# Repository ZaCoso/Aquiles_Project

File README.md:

# 🦿 AQUILES - Exoesqueleto de Asistencia Motriz

<div align="center">
  
  <h3>Revolucionando la movilidad humana</h3>
  <p>Exoesqueleto de asistencia motora con inteligencia artificial y control FOC</p>

  <p align="center">
    &nbsp;
    &nbsp;
    &nbsp;
    &nbsp;
    
  </p>
</div>

---

## 🌍 ¿Qué es AQUILES?

**AQUILES** es un exoesqueleto de asistencia motriz desarrollado por estudiantes de **Aviónica de la Escuela Técnica N.º 7 “IMPA” de Quilmes**, cuyo objetivo es **reducir la fatiga, mejorar la estabilidad y otorgar mayor autonomía** a personas con dificultades de movilidad.

El sistema combina **electrónica de control avanzada**, **inteligencia artificial adaptativa** y **una arquitectura de motores BLDC con control FOC**, optimizando la asistencia durante la marcha según el esfuerzo y ritmo del usuario.  
Incluye una **aplicación móvil y plataforma web** para el monitoreo, ajuste remoto y registro de datos clínicos en tiempo real.

---
## 🎬 Video Presentación
<p align="center">
  
  <br/>
  <em>Ver en YouTube</em>
</p>

---
## 🧠 Propósito e Impacto

AQUILES busca democratizar el acceso a tecnologías de rehabilitación avanzadas y accesibles en Argentina y Latinoamérica.  
Su impacto se extiende en tres ejes principales:

- **Médico:** mejora la eficacia de procesos de rehabilitación neuromotriz.  
- **Social:** promueve la autonomía e inclusión de personas con movilidad reducida.  
- **Tecnológico:** posiciona al país como referente en robótica de asistencia y salud.

---

## ⚙️ Arquitectura del Sistema

### 🔩 Hardware
- **Microcontrolador principal:** ESP32-S3 (Wi-Fi, BLE, USB OTG, dual-core LX7 240 MHz).  
- **Drivers de motor:** módulos basados en **IR2104 + MOSFETs IRLR7843** controlados por **RP2040**.  
- **Motores:** BLDC con reductoras planetarias de 4 etapas.  
- **Sensores:**
  - Encoders magnéticos **AS5600 / AS5048A**.  
  - Sensores de corriente **ACS725**.  
  - IMU **MPU-6050**.  
- **Fuente de alimentación:** baterías Li-Po 3S 5000 mAh 70C.  
- **Estructura:** piezas en **PETG** con insertos metálicos y módulos intercambiables (Athena, Drive-M, Módulos motrices).

### 💻 Software
- **Lenguajes:** C, C++, Dart, HTML, JS.  
- **Firmware:** SimpleFOC, comunicación SPI entre ESP32-S3 y RP2040.  
- **App móvil:** desarrollada en **Flutter + Firebase**, con UI intuitiva para monitoreo y ajustes.  
- **Web:** [zacas-code.github.io/Host_Aquiles_Project](https://zacas-code.github.io/Host_Aquiles_Project/) – presentación del ecosistema, galería, sponsors y contacto.

---

## 📱 Aplicación Móvil – *AquilesApp*

La app permite:
- Conectar el exoesqueleto vía BLE.  
- Ajustar el nivel de asistencia y sensibilidad.  
- Visualizar batería, torque y consumo en tiempo real.  
- Registrar sesiones de rehabilitación.  
- Generar informes automáticos para médicos y terapeutas.

Desarrollada en **Flutter**, con base de datos en **Firebase Firestore**, integración de **autenticación segura** y **almacenamiento en la nube**.

---

## 🦾 Módulos Principales

| Módulo | Descripción |
|--------|-------------|
| **Athena** | Núcleo de control. Alberga la mainboard, conectividad y algoritmo central. |
| **Drive-M** | Controladores locales con RP2040 + IR2104 + ACS725. |
| **Asistencia Motriz** | Transmisión de potencia con reductora planetaria 4 etapas. |
| **Aplicación** | Interfaz de control remoto y registro médico. |
| **Web** | Difusión, documentación y panel de desarrollo. |

---

## 🔋 Limitaciones y Próximos Pasos

### Limitaciones Actuales
- Autonomía limitada (≈45 min).  
- Calentamiento de motores en cargas elevadas.  
- Peso optimizable mediante nuevos materiales compuestos.

### Próximas Etapas
- Incorporación de **baterías modulares**.  
- Mejora del **control FOC con realimentación de corriente**.  
- Integración de **IA local** para detección de intención de paso.  
- Validación con pacientes y ensayos clínicos en centros de rehabilitación.

---

## 🧩 Stack Tecnológico

| Componente | Tecnología |
|-------------|-------------|
| **Microcontrolador** | ESP32-S3 (Espressif) |
| **Driver motor** | IR2104 + IRLR7843 |
| **Control local** | RP2040 |
| **Software embebido** | SimpleFOC, PlatformIO |
| **Aplicación móvil** | Flutter + Firebase |
| **Diseño mecánico** | Fusion 360 + impresión 3D PETG |
| **PCB** | EasyEDA Pro + KiCad |
| **Gestión** | Trello, Miro |

---

## 👨‍🔬 Equipo de Desarrollo

| Integrante | Contacto |
|-------------|-----------|
| **Juan Ignacio Montilla** | [GitHub](https://github.com/monti3) • [LinkedIn](https://www.linkedin.com/in/juan-ignacio-montilla-b98064358/) |
| **Santiago Alberto Zacarías** | [GitHub](https://github.com/ZaCoso) • [LinkedIn](https://www.linkedin.com/in/santiago-zacar%C3%ADas-3a3978319/) |
| **Juan Cruz Isola** | [GitHub](https://github.com/juanisola) • [LinkedIn](https://www.linkedin.com/in/juan-cruz-isola-11309035a/) |
| **Rodrigo Alexis Lin** | [GitHub](https://github.com/alexisrodrigolin) • [LinkedIn](https://www.linkedin.com/in/rodrigo-lin-61210a35b/) |
| **Mauricio Trillo Contardi** | [GitHub](https://github.com/MauricioTrillo) • [LinkedIn](https://www.linkedin.com/in/mauricio-trillo-contardi-68bbba35a/) |
| **Misael Castillo** | [GitHub](https://github.com/misaacastillo) • [LinkedIn](https://www.linkedin.com/in/misael-castillo-0a52a1314/) |

---

## 🙌 Agradecimientos

A los profesores **Diego Palmieri**, **Fabrizio Carlassara**, **Sergio Medina**, **Federico Solomiewicz**, **Carlos Bianco** y **Julián Scicolone** por su guía constante.  
Agradecemos también al **Centro Médico y de Rehabilitación del Sanatorio Modelo de Quilmes**, **Centro de Ojos Quilmes**, **Newton**, **Repuestos Santa Fe**, **La Amoladora Services**, **Ir3d**, **Mr Service**, **ElectroStar**, y **Decomontaje** por su apoyo técnico y material.

---

## 📜 Licencia

Este proyecto está bajo la licencia [MIT](LICENSE).  
© 2025 Aquiles Project — EEST N.º 7 “IMPA”, Quilmes.

---

> “AQUILES no es solo un proyecto tecnológico. Es una propuesta humana para devolver el movimiento, la autonomía y la esperanza.” 💪🦿

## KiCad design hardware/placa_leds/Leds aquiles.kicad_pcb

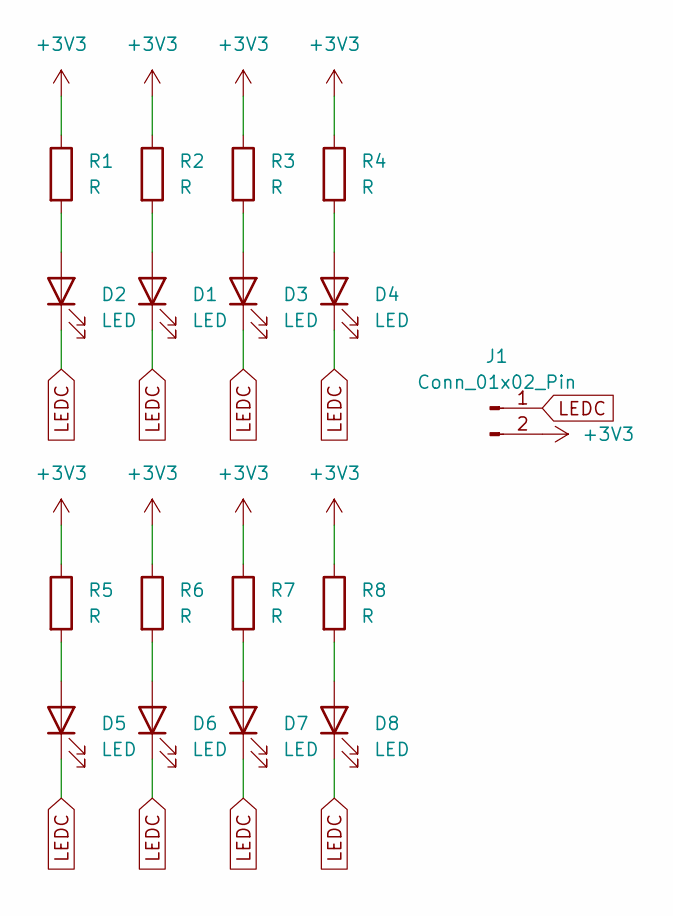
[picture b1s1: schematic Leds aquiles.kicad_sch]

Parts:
D1, D2, D3, D4, D5, D6, D7, D8: LED; LED_0805_2012Metric
J1: Conn_01x02_Pin; PinHeader_1x02_P2.54mm_Horizontal
R1, R2, R3, R4, R5, R6, R7, R8: R; R_0805_2012Metric

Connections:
+3V3: J1.2, R1.1, R2.1, R3.1, R4.1, R5.1, R6.1, R7.1, R8.1
LEDC: D1.1 (K), D2.1 (K), D3.1 (K), D4.1 (K), D5.1 (K), D6.1 (K), D7.1 (K), D8.1 (K), J1.1
unnamed: D1.2 (A), R2.2
unnamed: D2.2 (A), R1.2
unnamed: D3.2 (A), R3.2
unnamed: D4.2 (A), R4.2
unnamed: D5.2 (A), R5.2
unnamed: D6.2 (A), R6.2
unnamed: D7.2 (A), R7.2
unnamed: D8.2 (A), R8.2

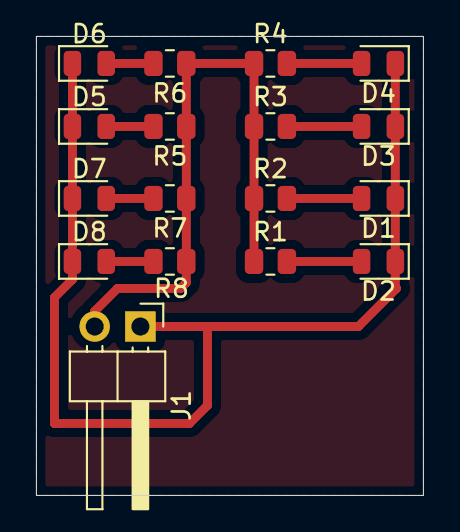
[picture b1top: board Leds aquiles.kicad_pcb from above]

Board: 2 copper layers, 21.5 x 25.5 mm, 17 parts (0 on the bottom side), 10 nets.

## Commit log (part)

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2025-08-08 Feat: Visual cue
2025-08-08 Feat: Carousel
2025-08-08 Fix: padding
2025-08-08 Fix: padding 2
2025-08-08 Fix: justify-content
2025-08-08 Fix: mobile google play button
2025-08-26 #6 fixes and feats
2025-08-26 refactor: cambio carpetas
2025-08-26 feat: open-loop control
2025-09-09 degree test
2025-09-09 chore: add foc example
2025-09-10 feat: Foc Adaptation
2025-09-10 feat: simplefoc testing .ino
2025-09-10 feat: FreeRtos init, Blink task
2025-09-14 fix: non running because of arduino version
2025-09-16 fix: Changing arduino version to earlyphilhower
2025-09-17 feat: testing code sensorless driver
2025-09-17 feat: current sensor tesing code
2025-09-17 feat: add code esp32s3 testing
2025-09-23 chore: change image mainscreen
2025-09-24 style:anado ui de iniciar sesion con google
2025-09-25 fix: soluciono problemas de merge
2025-09-25 fix: restauro archivos eliminados por error
2025-09-25 feat: add spi testing task
2025-09-25 fix: pin ch2
2025-09-25 fix: rp2040 pinout
2025-09-25 fix: crc bug
2025-09-26 fix: anado carpeta lib
2025-09-26 fix(style): reimplemento cambios en el login
2025-09-26 feat: implemento google services
2025-09-26 fix: Serial Monitor Bug
2025-09-27 style: agrega logo png
2025-09-27 feat: agrega nueva screen comienzo de tutorial de uso
2025-09-27 feat: agrega nueva screen ajuste espalda baja
2025-09-27 fix: arregla rutas entre screens
2025-09-29 refactor: extraigo widget step
2025-09-29 feat: anado screen ajuste faja
2025-09-29 feat: anada screen ajuste extensiones
2025-09-29 feat: anado screen final step
2025-09-29 style: implemento animacion transicion animatedSwitcher
2025-09-29 Feat: Aquiles primer prototipo logos
2025-10-01 feat: driver code feat: encoder Function
2025-10-01 refactor: function
2025-10-02 feat: mpu part
2025-10-02 refactor: mpu part
2025-10-02 Feat: Nuevos Sponsors
2025-10-02 Feat: Redesign de App movil
2025-10-02 feat: simple foc
2025-10-02 chore: Cambio de reconocimiento a trayectoria
2025-10-02 Feat: Linea de tiempo (espacio)
2025-10-02 Chore: orden alfabetico
2025-10-02 Chore: Nuevo logo
2025-10-02 Feat: trayectoria
2025-10-02 Chore: Location
2025-10-03 feat: diagrama
2025-10-04 Fix: Visible scroll
2025-10-04 chore: Perfiles
2025-10-04 feat: Double Spi code
2025-10-05 Feat: Timeline
2025-10-05 Feat: Perfil y Copiado del mail
2025-10-05 Chore: inset de box shadow
2025-10-05 Fix: bug visual del grid de .specs-grid
2025-10-05 Feat: Tegnologia avanzada
    -Arreglo de spec-panel
    -Boton de dar la vuelta
    -Cambio de imagen entre front y back
2025-10-05 Fix: dar la vuelta y cierre dinamico de menu desplegable
2025-10-05 Fix: ultimo sponsor impar Bug
2025-10-05 Fix: Futuros sponsors
2025-10-05 Fix: Sponsors y dar la vuelta
2025-10-05 Fix: Sponsors
2025-10-05 Feat: Arreglo Definitivo de Hotspot
2025-10-06 Chore: box-shadows
2025-10-06 Chore: diseño de contacto
2025-10-06 Chore: box-shadow: inset
2025-10-06 fix: encoder not reading (change i2c1)
2025-10-06 Feat: Descripciones
2025-10-06 Fix: Error visual
2025-10-06 Fix: Error visual 2
2025-10-07 Fix: texto Viejo
2025-10-07 Feat: Cambio de descripciones viejas
2025-10-07 fix: ble compatibility (change libs)
2025-10-07 reform: cambio a freertos
2025-10-07 fix: serial Bug
2025-10-07 feat: agrega screens nuevas
    Tutoriales con videos de como ponerse el exoesqueleto y como encenderlo. Cambios esteticos en la main screen.
2025-10-08 Chore: Nueva info de trayectoría
2025-10-08 Chore: Nuevas imagenes
2025-10-08 refactor(main): add namespace for better organization
2025-10-08 feat(main): Detection namespace
2025-10-08 Feat: Diseño y Arreglo definitivo de Hotspot
2025-10-08 Chore: Descripción vieja del Módulo Athena
2025-10-08 Fix: ajuste de zoom
2025-10-08 Fix: Zoom solo para index
2025-10-08 Fix: App display
    Muy a la derecha
2025-10-09 Fix: App display 2
2025-10-09 feat: agrega screen busqueda BLE
2025-10-09 testing: implemento mock de BLE service
2025-10-10 refactor: rewrite SPIBus
2025-10-10 refactor (driver): rewrite DriverSpi
2025-10-10 feat(driver): adapt spi to encoder and mpu
2025-10-11 Refactor(driver): borro parte de encoder 5048
2025-10-11 refactor(driver): elimino control foc por angulo
2025-10-11 feat(main): conexion entre spi y detecicon
2025-10-11 feat(driver): implementacion de spi con simplefoc
2025-10-11 fix: doble variable problem
2025-10-11 feat: Funcion de Sensor de Intensidad
2025-10-11 fix error
2025-10-12 fix(main): Desconfiguracion por pin 46 (se reseteaba)
2025-10-12 fix: pines de spi
2025-10-12 fix: error
2025-10-12 fix:spi channel meassure
2025-10-12 fix(driver): stacking because of isr
2025-10-12 fix: spi checking
2025-10-12 fix(driver): change pins of spi
2025-10-13 feat(main): add power options
2025-10-13 feat(main): adapt power options to ble
2025-10-13 fix(main): change adc pinout
2025-10-13 feat(main): add safety button spu interrup
2025-10-13 feat(driver):add spi-stop security
2025-10-13 fix: spi pin
2025-10-13 feat: add leds function
2025-10-13 fix: lagueo por serial (isr)
2025-10-13 feat: add testing code
2025-10-14 reafactor: spi to uart multiplexed
2025-10-14 refactor: uart-multiplexor to uart-dual
2025-10-14 refactor= Serial Uart- GpUart
2025-10-14 feat: Uart testing code
2025-10-14 feat: Serial Print
2025-10-14 feat: central mpu integration
2025-10-14 fix: change of board
2025-10-14 reafactor: elimino funciones de imu en driver
2025-10-14 feat: adaptacion de nuevo paquete de datos
2025-10-14 feat: adaptacion de main de version de paquete v2
2025-10-14 style: cambio fondo bottomnav
2025-10-14 docs: actualizo readme
2025-10-15 testing: se establece flag para fakeBLE
2025-10-15 refactor(central): migrate NimBLE to BLE
2025-10-15 refactor: delete unfunctional code
2025-10-16 fix: change pull down to pull up
2025-10-16 fix: change button to cs2
2025-10-16 test: comento funcion de ppaquete grande de ble
2025-10-16 feat: breathing-led function
2025-10-16 fix: correct activation mode
2025-10-16 feat: encoder value print
2025-10-16 refactor: valores de telemetry que no uso a 0
2025-10-16 refactor: cambio el color del rgb a color aquiles
2025-10-16 fix: change service
2025-10-16 fix: ble bug solucionado
2025-10-16 feat: anado nuevos uuid
2025-10-16 feat: creo las caracteristicas
2025-10-16 feat: add carrachteristic notification
2025-10-16 refactor: reorient power options
2025-10-16 fix: put right pins
2025-10-21 feat: Añadir archivos de diseño
2025-10-24 feat: carpeta tecnica y de campo
2025-10-24 Feat: Añadir los posts de Ig
2025-10-24 Feat: Perfiles de integrantes de Aquiles
2025-10-24 Fix: PNG en mayusculas
    error con host
2025-10-24 Fix: zoom de Reconocimientos
2025-10-24 Fix: Conflicto de mobile view con padding
2025-10-24 Chore: ortografia
2025-10-24 Chore: .PNG images
2025-10-24 Chore: zoom
2025-10-24 Fix: logo in mobile view
2025-10-24 Feat: Medallero
2025-10-24 Fix: zoom para mobile view
2025-10-24 Feat: Iphone 16
    Cambio de iphone viejo a iphone 16 de la app movil
2025-10-24 Fix: exo-skeleton image
2025-10-24 Fix: Títulos e Imagenes
2025-10-25 Fix: drop-shadow de todas las <img>
2025-10-25 Chore: drop-shadow en mobile view
2025-10-25 Chore: Wrong Value
2025-10-25 Fix: centered logo in mobile and desktop view
2025-10-27 Chore: link to APP.apk
2025-10-31 feat/ informe descriptivo ONIET
2025-10-31 Nuevos Posts
2025-10-31 feat/ Informe Aquiles App Sysapp
2025-10-31 feat(ble): centralize UUIDs and sensor metadata in config and refactor BLE consumers
2025-10-31 refactor(ble): introduce BleClient interface and unify real/fake BLE services
2025-10-31 feat(ui): improve telemetry labels and debug info using shared BLE config
2025-10-31 chore(platform): update Gradle, SDK targets, and iOS xcconfig for Flutter 3.24
2025-10-31 chore: apply const constructors, clean imports and improve auth error handling
2025-10-31 test: wrap AquilesApp
2025-10-31 Añadir destacadas de Instagram
2025-10-31 feat(auth): add Firebase email registration support
2025-10-31 feat(ui): add register screen and navigation entry points
2025-10-31 feat(auth): support password reset via email
2025-10-31 feat(ui): add register and password reset screens
2025-10-31 docs: add license
2025-11-01 feat: ble example esp32 side
2025-11-03 refactor: Comment and Reorder AppTasks.h
2025-11-03 refactor: Comment and reorder AppTasks.cpp
2025-11-03 refactor: Comment and reorder main.cpp
2025-11-03 refactor: reorder and comment Driver_code
2025-11-03 fix(central): Ble declaration Bug
2025-11-03 chore: añado cache
2025-11-03 chore: añado pcb
2025-11-03 chore: añado prl
2025-11-03 chore: añado pro
2025-11-03 chore: añado sch
2025-11-03 feat: disconnection button implementation
2025-11-04 feat: add connector board
2025-11-04 fest: add bldc driver 1.0
2025-11-04 fest: add bldc driver 2.0
2025-11-04 fest: add bldc driver 3.0
2025-11-04 fest: add bldc driver 4.0
2025-11-04 refactor: driver 2.0 was 2.1
2025-11-04 fest: add bldc driver 4.1
2025-11-04 feat: mainboard
2025-11-04 chore: add .epro to mainboard
2025-11-04 feat: mainboard w shunts
2025-11-04 feat: mainboard w shunts 2.0
2025-11-04 feat: mainboard w shunts 3.0
2025-11-04 chore: chango mainboard shunts 3.0 to epro
2025-11-05 feat: cambiar carpeta
2025-11-07 fix: correct telemetryV2
2025-11-07 fix: escala de comando de velocidad y flacg de OC
2025-11-07 feat: Añadir historias recientes
2025-11-07 feat: logger mode for deteccion
2025-11-08 fix: handle receiving issues
2025-11-08 Feat: Se agrego el iframe del video de presentación
2025-11-08 Chore: Orden de la pagina
2025-11-08 feat: ble buzzer
2025-11-08 fix: ble formato de paquetes
2025-11-08 test: test mode==true
2025-11-08 feat BLE caracteristicas y streamenabled
2025-11-08 feat: modo de prueba para Ble
2025-11-08 fix: testing code
2025-11-08 fix: handle recwiving issues
2025-11-08 fix(central): ble functions
2025-11-08 Chore: datos
2025-11-08 Chore: Transferencia de datos
2025-11-08 Feat: video de youtube y sponsors
    .
2025-11-08 example: buzzer song
2025-11-08 example: buzzer ledc
2025-11-08 chore:rename buzzer example
2025-11-08 Chore: carpeta sin uso
2025-11-08 fix: buzzer problem
2025-11-08 feat: add different type of sounds to buzzer
2025-11-08 Address erronea
